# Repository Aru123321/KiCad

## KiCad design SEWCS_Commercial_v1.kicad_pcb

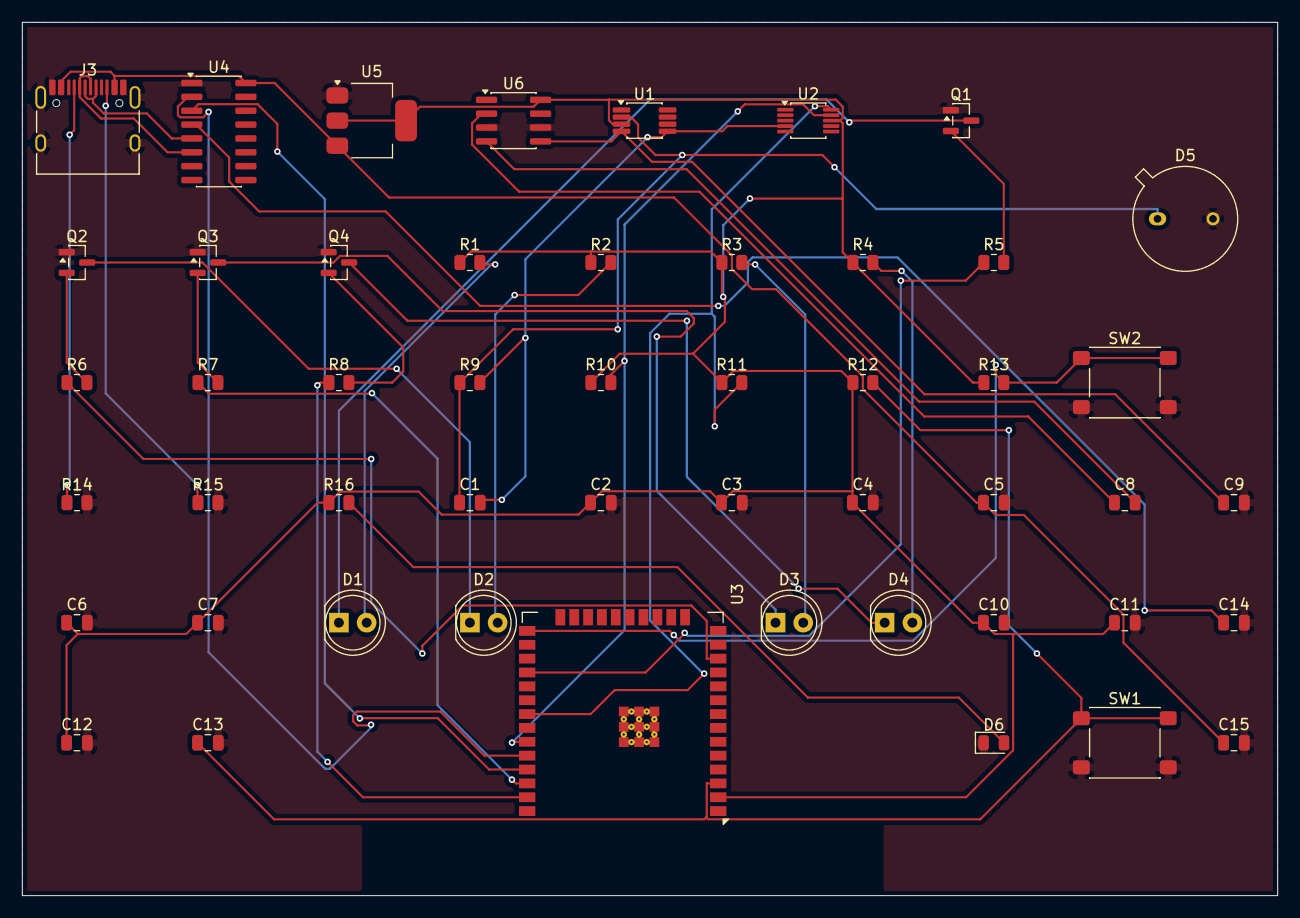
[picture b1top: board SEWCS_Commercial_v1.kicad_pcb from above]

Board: 2 copper layers, 115.0 x 80.0 mm, 50 parts (0 on the bottom side), 36 nets.

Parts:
C1: 2.2p; C_0805_2012Metric
C2, C3, C7, C10, C11, C13, C14, C15: 100n; C_0805_2012Metric
C4, C5, C8, C9, C12: 10u; C_0805_2012Metric
C6: 22u; C_0805_2012Metric
D1: LED910L; LED_D5.0mm
D2: LED1085L; LED_D5.0mm
D3: LED1300L; LED_D5.0mm
D4: LED1600L; LED_D5.0mm
D5: FDG05; TO-5-2_Window
D6: PWR; LED_0805_2012Metric
J3: USB-C; USB_C_Receptacle_HRO_TYPE-C-31-M-12
Q1, Q2, Q3, Q4: 2N7002; SOT-23
R1: 150; R_0805_2012Metric
R2: 180; R_0805_2012Metric
R3: 200; R_0805_2012Metric
R4: 220; R_0805_2012Metric
R5, R6, R7, R8: 100; R_0805_2012Metric
R9: 100k; R_0805_2012Metric
R10, R11, R12, R13: 10k; R_0805_2012Metric
R14, R15: 5.1k; R_0805_2012Metric
R16: 1k; R_0805_2012Metric
SW1: RESET; SW_SPST_PTS645Sx43SMTR92
SW2: BOOT; SW_SPST_PTS645Sx43SMTR92
U1: OPA380AID; VSSOP-8_3x3mm_P0.65mm
U2: ADS1115_Breakout; MSOP-10_3x3mm_P0.5mm
U3: ESP32-WROOM-32E
U4: CH340C; SOIC-16_3.9x9.9mm_P1.27mm
U5: AMS1117-3.3; SOT-223-3_TabPin2
U6: ICL7660; SOIC-8_3.9x4.9mm_P1.27mm

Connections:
+3V3: C2.1, C3.1, C4.1, C6.1, C7.1, C10.1, C11.1, C12.1, R1.1, R2.1, R3.1, R4.1, R10.1, R11.1, R12.1, R13.1, R16.1, U1.3, U2.8, U3.2, U5.2, U6.8
+5V: C5.1, C15.1, J3.A4, J3.A9, J3.B4, J3.B9, U4.16, U5.3
-3V3: C9.1, U1.4, U6.5
CC1: J3.A5, R14.1
CC2: J3.B5, R15.1
CP_MINUS: C8.2, U6.4
CP_PLUS: C8.1, U6.2
EN: C13.1, R12.2, SW1.1, U3.3
ESP_RX: U3.34, U4.2
ESP_TX: U3.35, U4.3
GND: C2.2, C3.2, C4.2, C5.2, C6.2, C7.2, C9.2, C10.2, C11.2, C12.2, C13.2, C14.2, C15.2, D5.2, D6.1, J3.A1, J3.A12, J3.B1, J3.B12, J3.SH, Q1.1, Q2.1, Q3.1, Q4.1, R14.2, R15.2, SW1.2, SW2.2, U1.1, U2.1, U2.3, U4.1, U5.1, U6.3, U6.6
GPIO17: R5.1, U3.28
GPIO22: R7.1, U3.36
GPIO23: R8.1, U3.37
GPIO27: R6.1, U3.12
I2C_SCL: R11.2, U2.10, U3.31
I2C_SDA: R10.2, U2.9, U3.33
IO0: R13.2, SW2.1, U3.25
LED910_A: D1.2, R1.2
LED910_K: D1.1, Q1.3
LED1085_A: D2.2, R2.2
LED1085_K: D2.1, Q2.3
LED1300_A: D3.2, R3.2
LED1300_K: D3.1, Q3.3
LED1600_A: D4.2, R4.2
LED1600_K: D4.1, Q4.3
PD_SIG: C1.1, D5.1, R9.1, U1.2
PWR_LED: D6.2, R16.2
Q1_GATE: Q1.2, R5.2
Q2_GATE: Q2.2, R6.2
Q3_GATE: Q3.2, R7.2
Q4_GATE: Q4.2, R8.2
TIA_OUT: C1.2, R9.2, U1.5, U2.4
USB_DM: J3.A7, J3.B7, U4.6
USB_DP: J3.A6, J3.B6, U4.5
V3_CH340: C14.1, U4.4

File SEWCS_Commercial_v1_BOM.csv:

value,footprint,quantity,references
ADS1115_Breakout,Package_SO:MSOP-10_3x3mm_P0.5mm,1,['U2']
OPA380AID,Package_SO:VSSOP-8_3x3mm_P0.65mm,1,['U1']
BOOT,Button_Switch_SMD:SW_SPST_PTS645Sx43SMTR92,1,['SW2']
RESET,Button_Switch_SMD:SW_SPST_PTS645Sx43SMTR92,1,['SW1']
100n,Capacitor_SMD:C_0805_2012Metric,8,"['C13', 'C7', 'C2', 'C14', 'C10', 'C11', 'C3', 'C15']"
2N7002,Package_TO_SOT_SMD:SOT-23,4,"['Q2', 'Q4', 'Q3', 'Q1']"
200,Resistor_SMD:R_0805_2012Metric,1,['R3']
10u,Capacitor_SMD:C_0805_2012Metric,5,"['C12', 'C9', 'C8', 'C4', 'C5']"
10k,Resistor_SMD:R_0805_2012Metric,4,"['R13', 'R12', 'R11', 'R10']"
100,Resistor_SMD:R_0805_2012Metric,4,"['R5', 'R8', 'R7', 'R6']"
ESP32-WROOM-32E,RF_Module:ESP32-WROOM-32E,1,['U3']
LED910L,LED_THT:LED_D5.0mm,1,['D1']
5.1k,Resistor_SMD:R_0805_2012Metric,2,"['R15', 'R14']"
CH340C,Package_SO:SOIC-16_3.9x9.9mm_P1.27mm,1,['U4']
AMS1117-3.3,Package_TO_SOT_SMD:SOT-223-3_TabPin2,1,['U5']
100k,Resistor_SMD:R_0805_2012Metric,1,['R9']
180,Resistor_SMD:R_0805_2012Metric,1,['R2']
FDG05,Package_TO_SOT_THT:TO-5-2_Window,1,['D5']
22u,Capacitor_SMD:C_0805_2012Metric,1,['C6']
150,Resistor_SMD:R_0805_2012Metric,1,['R1']
LED1085L,LED_THT:LED_D5.0mm,1,['D2']
LED1600L,LED_THT:LED_D5.0mm,1,['D4']
2.2p,Capacitor_SMD:C_0805_2012Metric,1,['C1']
ICL7660,Package_SO:SOIC-8_3.9x4.9mm_P1.27mm,1,['U6']
LED1300L,LED_THT:LED_D5.0mm,1,['D3']
1k,Resistor_SMD:R_0805_2012Metric,1,['R16']
PWR,LED_SMD:LED_0805_2012Metric,1,['D6']
USB-C,Connector_USB:USB_C_Receptacle_HRO_TYPE-C-31-M-12,1,['J3']
220,Resistor_SMD:R_0805_2012Metric,1,['R4']

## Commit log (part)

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2026-06-14 sewcs_KiCadIteration_1
2026-06-29 Add commercial ESP32 board (SEWCS_Commercial_v1): schematic, routed PCB, fab package, BOM; knowledge base; gitignore
2026-06-29 Document optics-head architecture decision, v1 freeze + v1.1 roadmap, and validate-first sequencing
2026-06-29 Add JLCPCB-ready PCBA BOM with LCSC part numbers; optics marked DNP
